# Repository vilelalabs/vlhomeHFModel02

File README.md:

# VLHOME Hardware Firmware - MODEL 02

Remotely activated device through Wifi connection with a Firebase database.

## Project

This software was developed to be used on ESP8266-12 (4Mb flash) microcontroller to controls a high voltage device and connecting to a physical activated switch.

## Operation

the device can be activated through three ways:

### > Application
Through using dedicated Application:  [VLHome App](https://github.com/vilelalabs/vlhome) 

### > Webpage
Through webpage using the addresses:

|Link |Function|
|:----------:|:----------:|
|http://device-IPAdress/|home page that confirms the connection|
|http://device-IPAdress/update|update through OTA|
|http://device-IPAdress/toggle|toggles the current state of the device|
|http://device-IPAdress/hostname|shows the host name of the device|

> example: http://192.168.1.225/update

### > Switch

Can be physically actvated bt the switch linked to CON1 (SWITCH) connector onboard (see images) - this connection is optional.

# Installation 

Until now (version: 1.0) its needed to use an auxiliar application from Espressif to connect the device to the local network. The application used is [EspTouch: SmartConfig for ESP ESP8266, ESP32](https://play.google.com/store/apps/details?id=com.khoazero123.iot_esptouch_demo). On it you will need to put the SSID and password information.

After some time the device is found and it shows the IP address, take note to use the webpage activation method, or even to compare to new device configuration screen (*Novo Dispositivo*) through [App](https://github.com/vilelalabs/vlhome).

From this point  **webpage** and **switch** methods can be used already , but on the **App**, you still need use the menu before: 

**Configurações > Dispositivos > Novo > Buscar Novo Dispositivo**

# Folder eaglefiles

In this folder you will find the necessary files for building the hardware board: 

- Eagle project
- Schematic file (SCH)
- Board file (PCB layout) (BRD) (between the two projects - one/two side only capacitor package is different)
- Bill of Materials file (BOM)
- PDF file with a ready-for-printing page with the board layout.
- MODEL_2_Gerber.zip for sent to a professinal fabrication

_* there is two versions for one side cooper and Double Layer  boards, see by file names_
# Images

## Schematic

## Board (PCB)

### Double Layer  Board (PCB)
|Top Side |Bottom side|
|:----------:|:----------:|
|||
## 3D View
|Top Side - Single Cooper |Bottom side - Single Cooper|
|:----------:|:----------:|
|||
|Top Side - Double Layer Cooper|Bottom side - Double Layer Cooper|
|||

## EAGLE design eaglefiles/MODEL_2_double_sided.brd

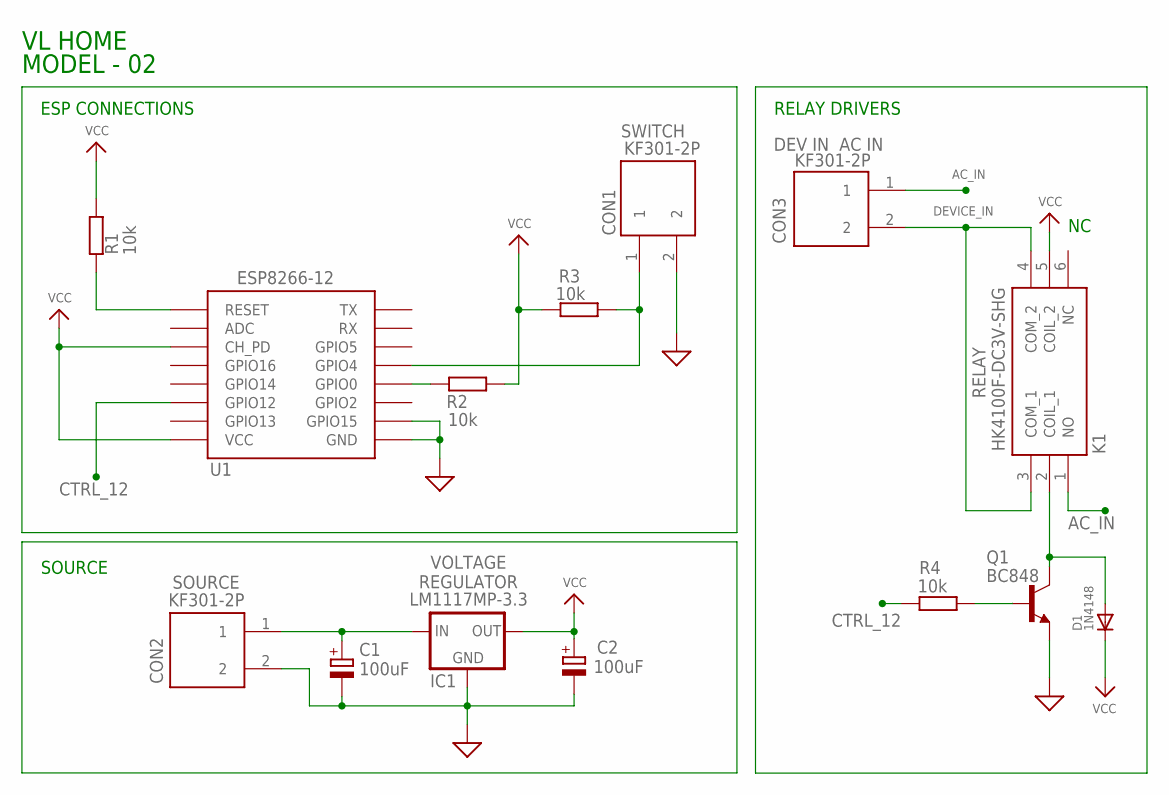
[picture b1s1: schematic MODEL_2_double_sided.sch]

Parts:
C1, C2: 100uF; UD-6,3X7,7_NICHICON
CON1, CON2, CON3: KF301-2P; HANDSON_KF301-2P
D1: 1N4148; SOD80_DO213AA_MINIMELF
IC1: LM1117MP-3.3; SOT223
K1: HK4100F-DC3V-SHG; HK4100FDC5VSHG
Q1: BC848; SOT23
R1, R2, R3, R4: 10k; R0805
U1: ESP8266-12; ESP12-SMD

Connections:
AC_IN: CON3.1, K1.1 (NO)
CTRL_12: R4.2, U1.GPIO12
DEVICE_IN: CON3.2, K1.3 (COM_1), K1.4 (COM_2)
GND: C1.-, C2.-, CON1.2, CON2.2, IC1.1 (GND), Q1.2 (E), U1.GND, U1.GPIO15
unnamed: R1.1, U1.RESET
unnamed: CON1.1, R3.1, U1.GPIO4
unnamed: Q1.1 (B), R4.1
unnamed: R2.1, U1.GPIO0
unnamed: D1.A, K1.2 (COIL_1), Q1.3 (C)
unnamed: C1.+, CON2.1, IC1.3 (IN)
VCC: C2.+, D1.C, IC1.2 (OUT), IC1.4 (OUT), K1.5 (COIL_2), R1.2, R2.2, R3.2, U1.CH_PD, U1.VCC

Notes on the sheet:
ESP CONNECTIONS
SOURCE
RELAY DRIVERS
MODEL - 02
VL HOME
SWITCH
CON3
DEV IN AC IN
RELAY
VOLTAGE REGULATOR

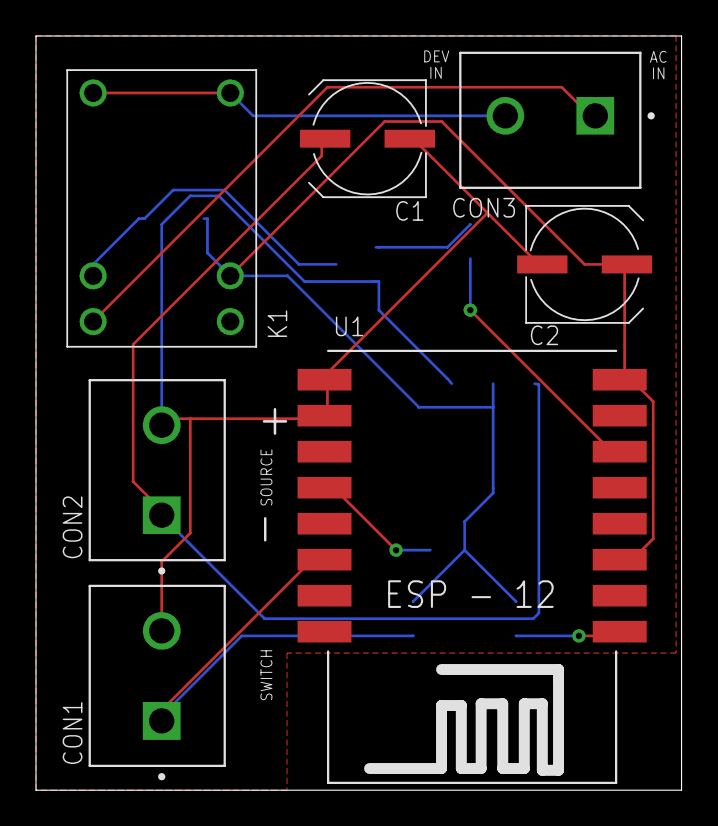
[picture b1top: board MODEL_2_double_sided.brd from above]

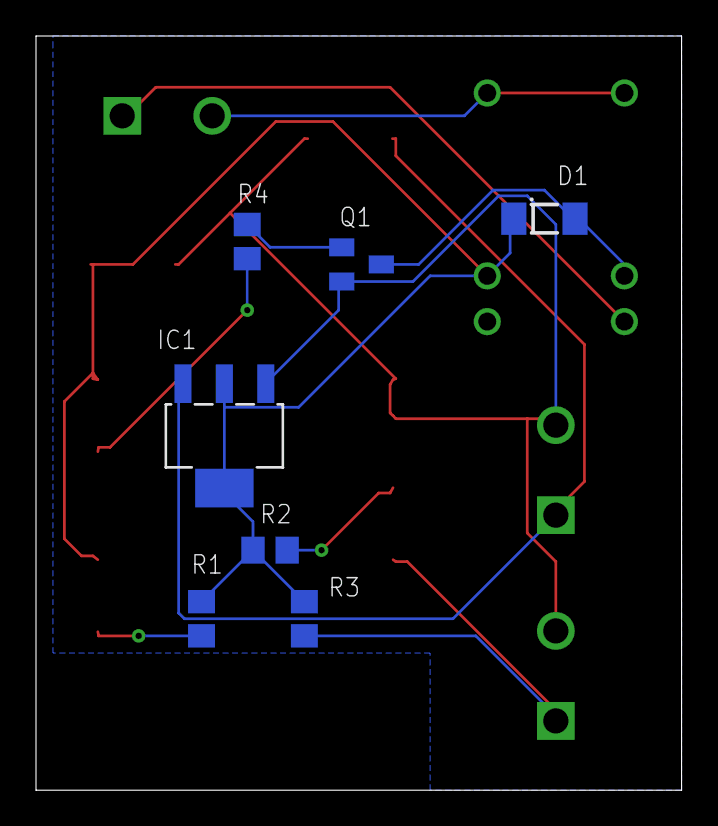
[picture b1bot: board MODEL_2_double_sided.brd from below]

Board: 2 copper layers, 35.9 x 41.9 mm, 14 parts (7 on the bottom side), 11 nets.

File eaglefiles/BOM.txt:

Part List

Part Value            Device           Package          Description                                  
C1   100uF            CPOL-EUE2.5-7    E2,5-7           POLARIZED CAPACITOR, European symbol         
C2   100uF            CPOL-EUE2.5-7    E2,5-7           POLARIZED CAPACITOR, European symbol         
CON1 KF301-2P         KF301-2P         KF301-2P         2 Pin Terminal Block 5mm Pitch Check prices  
CON2 KF301-2P         KF301-2P         KF301-2P         2 Pin Terminal Block 5mm Pitch Check prices  
CON3 KF301-2P         KF301-2P         KF301-2P         2 Pin Terminal Block 5mm Pitch Check prices  
D1   1N4148           LL4148           SOD80            1N4148 General Purpose Rectifie              
IC1  LM1117MP-3.3     LM1117MP-3.3     SOT223           800mA Low-Dropout Linear Regulator           
K1   HK4100F-DC3V-SHG HK4100F-DC3V-SHG HK4100FDC3VSHG   Relays Gen Purpose 3.3VDC SPDT 3A (250VAC , 30VDC)
Q1   BC848            BC848            SOT23            NPN TRANSISTOR                              
R1   10k              R-EU_R0805       R0805            RESISTOR, European symbol                        
R2   10k              R-EU_R0805       R0805            RESISTOR, European symbol                        
R3   10k              R-EU_R0805       R0805            RESISTOR, European symbol                        
R4   10k              R-EU_R0805       R0805            RESISTOR, European symbol                        
U1   ESP8266-12       ESP12F           ESP12F           ESP8266 12F SMD mount

* R1, R2 and R3 can be changed for similar values when mounting.

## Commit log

2022-04-26 changing switch input to pin 5
2022-04-26 change switch to pin 5
2022-05-03 changed GPIO5 -> GPIO4
2022-05-04 readme images upload
2022-05-04 Eagle files upload
2022-05-04 adding BOM to files
2022-05-04 update BOM
2022-05-04 README English translation
2022-05-12 double-sided project images
2022-05-12 double sided project files upload
2022-05-12 Added double sided board files and images
2022-05-13 Add gerber file
2022-05-13 READme updates
